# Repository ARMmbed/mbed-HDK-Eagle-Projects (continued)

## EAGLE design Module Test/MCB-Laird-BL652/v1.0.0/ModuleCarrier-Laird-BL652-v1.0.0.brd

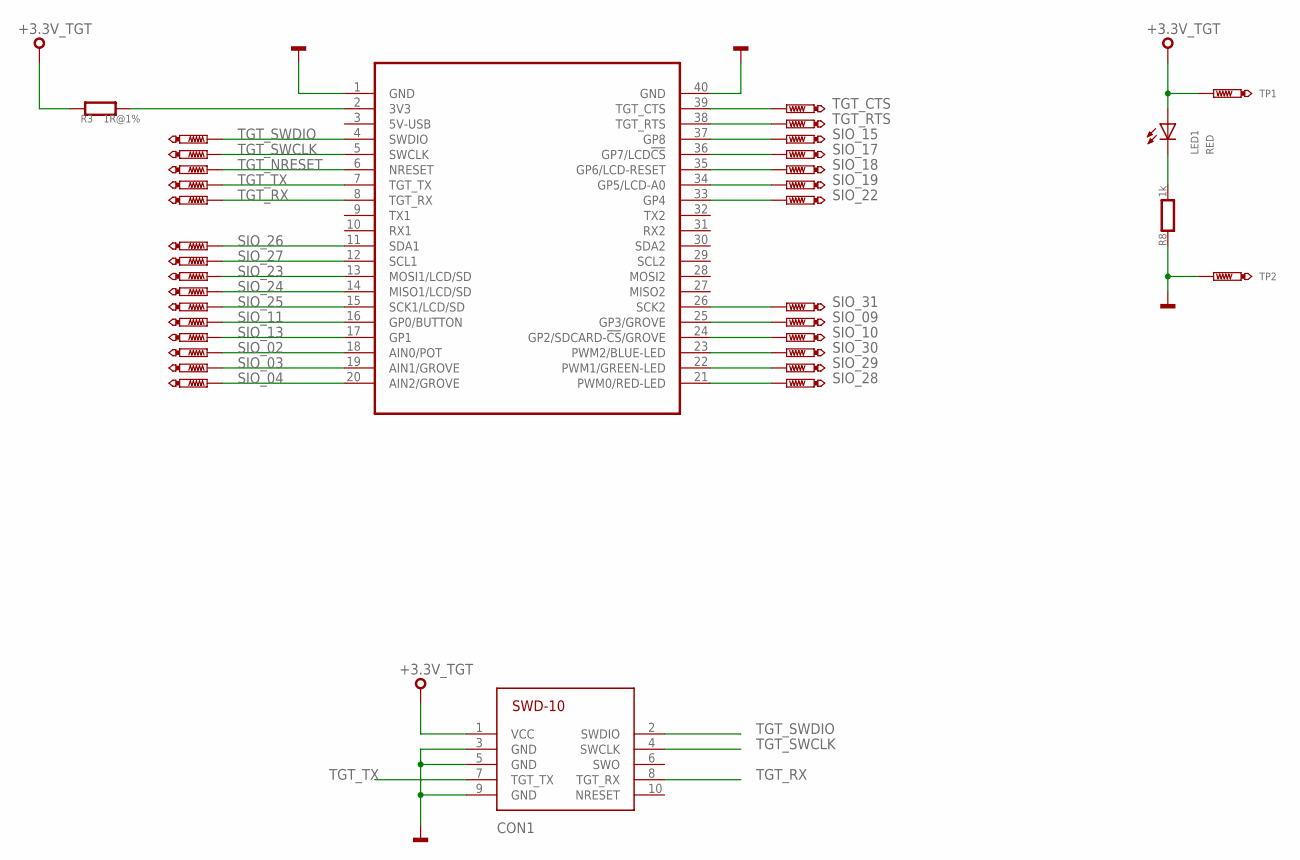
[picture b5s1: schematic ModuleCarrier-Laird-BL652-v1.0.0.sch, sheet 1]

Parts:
CON1: SWD-10/TC2050_SMD; FTSH-105-02
LED1: RED; CHIPLED_0603
MOD2: MODULE_DAUGHTER
R3: 1R@1%; 0603
R8: 1k; 0603
TP1, TP2: TEST-POINT-50R-PTH; TP50-PTH
TP3, TP4, TP5, TP6, TP7, TP8, TP9, TP10, TP11, TP12, TP13, TP14, TP15, TP16, TP17, TP18, TP19, TP20, TP21, TP22, TP23, TP24, TP25, TP26, TP27, TP28, TP29, TP30: PTR1TP07R; TP07R

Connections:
+3.3V_TGT: CON1.1 (VCC), LED1.A, R3.1, TP1.TP; also elsewhere on the board
GND: CON1.3 (GND), CON1.5 (GND), CON1.9 (GND), MOD2.1 (GND), MOD2.40 (GND), R8.1, TP2.TP; also elsewhere on the board
unnamed: MOD2.2 (3V3), R3.2
PA_1: LED1.C, R8.2
SIO_02: MOD2.18 (AIN0/POT), TP10.TP; also elsewhere on the board
SIO_03: MOD2.19 (AIN1/GROVE), TP11.TP; also elsewhere on the board
SIO_04: MOD2.20 (AIN2/GROVE), TP12.TP; also elsewhere on the board
SIO_09: MOD2.25 (GP3/GROVE), TP17.TP; also elsewhere on the board
SIO_10: MOD2.24 (GP2/SDCARD-!CS!/GROVE), TP16.TP; also elsewhere on the board
SIO_11: MOD2.16 (GP0/BUTTON), TP8.TP; also elsewhere on the board
SIO_13: MOD2.17 (GP1), TP9.TP; also elsewhere on the board
SIO_15: MOD2.37 (GP8), TP22.TP; also elsewhere on the board
SIO_17: MOD2.36 (GP7/LCD!CS), TP21.TP; also elsewhere on the board
SIO_18: MOD2.35 (GP6/LCD-RESET), TP20.TP; also elsewhere on the board
SIO_19: MOD2.34 (GP5/LCD-A0), TP19.TP; also elsewhere on the board
SIO_22: MOD2.33 (GP4), TP18.TP; also elsewhere on the board
SIO_23: MOD2.13 (MOSI1/LCD/SD), TP5.TP; also elsewhere on the board
SIO_24: MOD2.14 (MISO1/LCD/SD), TP6.TP; also elsewhere on the board
SIO_25: MOD2.15 (SCK1/LCD/SD), TP7.TP; also elsewhere on the board
SIO_26: MOD2.11 (SDA1), TP3.TP; also elsewhere on the board
SIO_27: MOD2.12 (SCL1), TP4.TP; also elsewhere on the board
SIO_28: MOD2.21 (PWM0/RED-LED), TP13.TP; also elsewhere on the board
SIO_29: MOD2.22 (PWM1/GREEN-LED), TP14.TP; also elsewhere on the board
SIO_30: MOD2.23 (PWM2/BLUE-LED), TP15.TP; also elsewhere on the board
SIO_31: MOD2.26 (SCK2), TP25.TP; also elsewhere on the board
TGT_CTS: MOD2.39 (TGT_CTS), TP24.TP; also elsewhere on the board
TGT_NRESET: MOD2.6 (NRESET), TP28.TP; also elsewhere on the board
TGT_RTS: MOD2.38 (TGT_RTS), TP23.TP; also elsewhere on the board
TGT_RX: CON1.8 (TGT_RX), MOD2.8 (TGT_RX), TP30.TP; also elsewhere on the board
TGT_SWCLK: CON1.4 (SWCLK), MOD2.5 (SWCLK), TP27.TP; also elsewhere on the board
TGT_SWDIO: CON1.2 (SWDIO), MOD2.4 (SWDIO), TP26.TP; also elsewhere on the board
TGT_TX: CON1.7 (TGT_TX), MOD2.7 (TGT_TX), TP29.TP; also elsewhere on the board

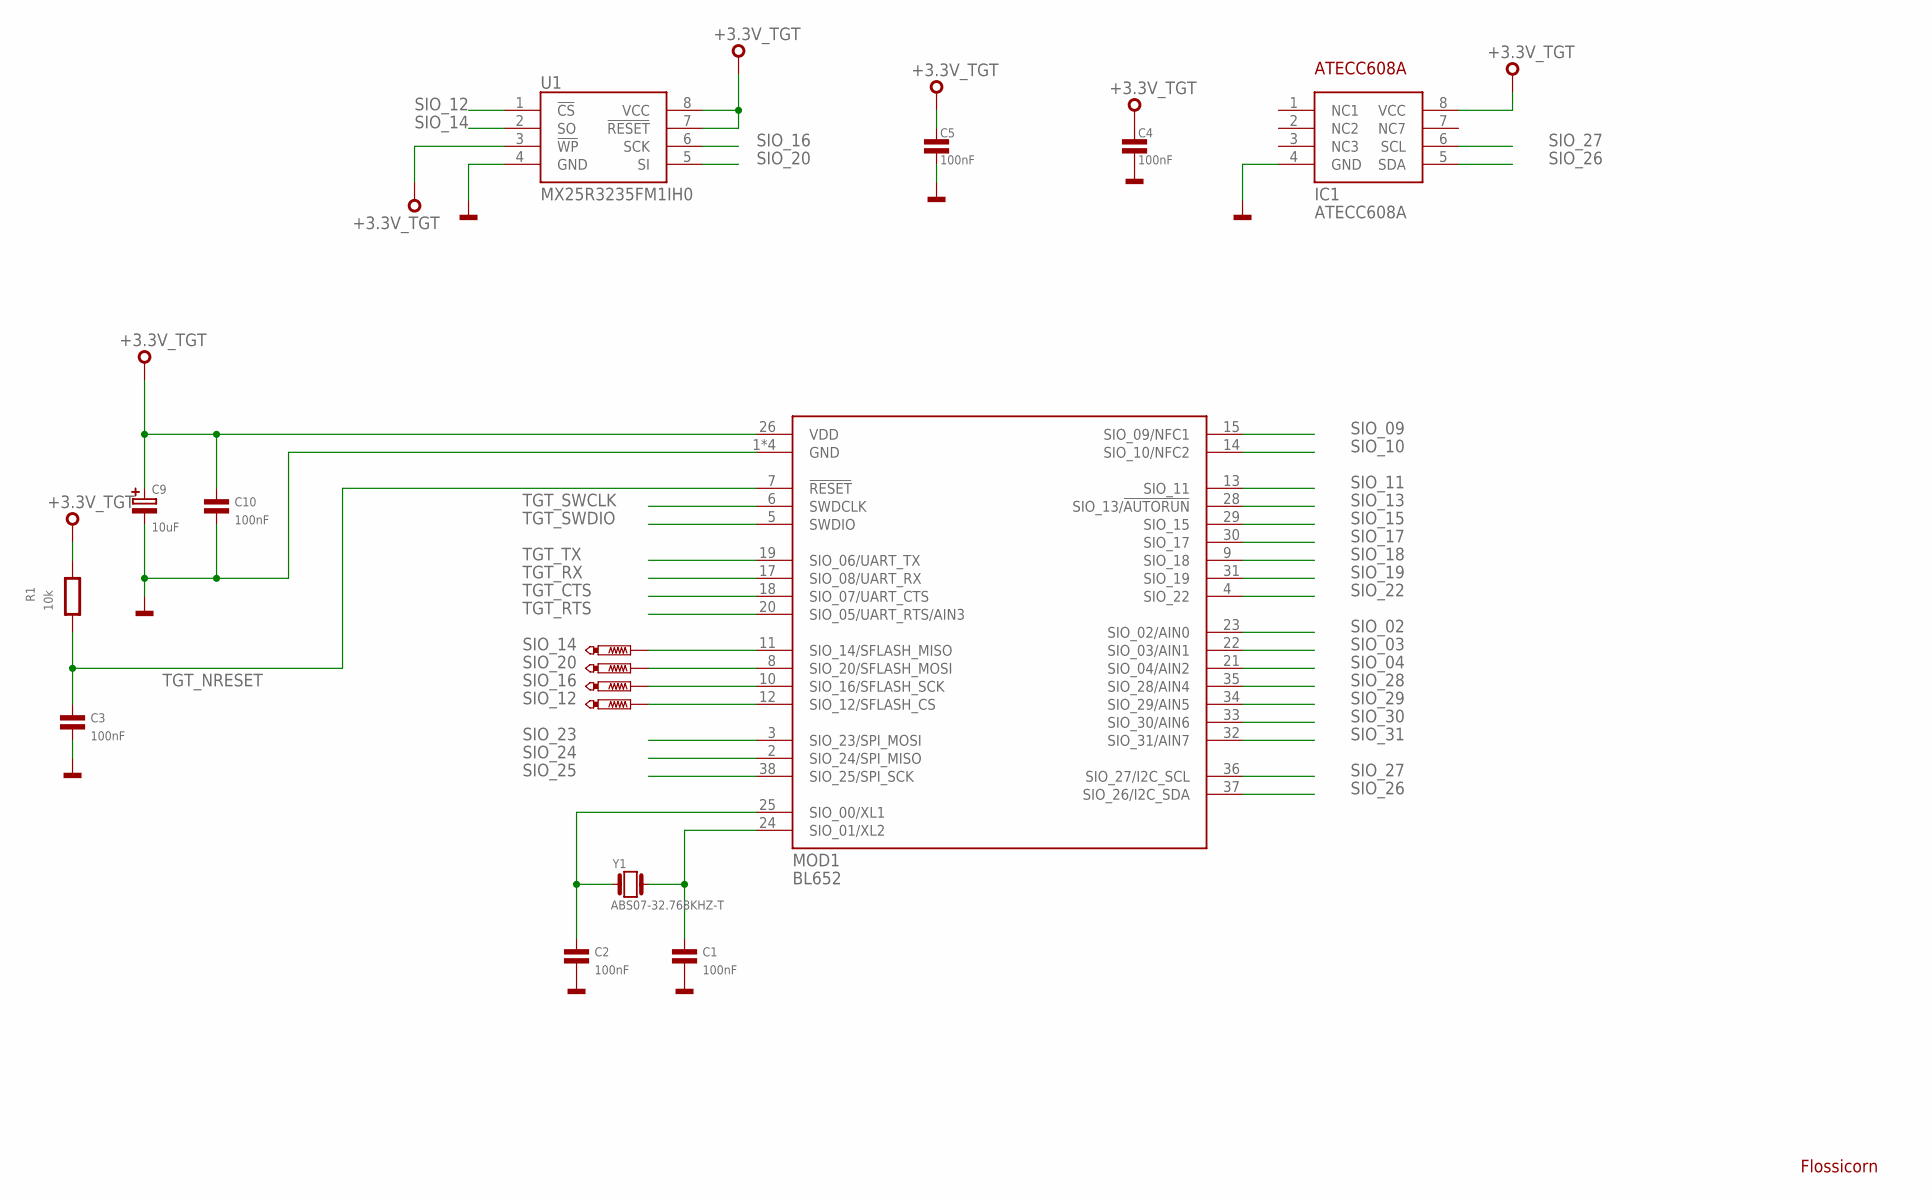
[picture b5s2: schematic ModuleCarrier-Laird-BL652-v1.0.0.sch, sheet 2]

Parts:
C1, C2, C3, C4, C5, C10: 100nF; 0603
C9: 10uF; CASE-B
IC1: ATECC608A; SO8
MOD1: BL652
R1: 10k; 0603
SS1: FLOSSICORN0.25; FLOSSICORN-0.25
TP31, TP32, TP33, TP34: PTR1TP07R; TP07R
U1: MX25R3235FM1IH0; SO8
Y1: ABS07-32.768KHZ-T; FC135

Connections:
+3.3V_TGT: C4.1, C5.1, C9.1, C10.1, IC1.8 (VCC), MOD1.26 (VDD), R1.2, U1.3 (!WP), U1.7 (!RESET), U1.8 (VCC); also elsewhere on the board
GND: C1.2, C2.2, C3.2, C4.2, C5.2, C9.2, C10.2, IC1.4 (GND), MOD1.1 (GND), MOD1.16 (GND), MOD1.27 (GND), MOD1.39 (GND), U1.4 (GND); also elsewhere on the board
unnamed: C1.1, MOD1.24 (SIO_01/XL2), Y1.X2 (2)
unnamed: C2.1, MOD1.25 (SIO_00/XL1), Y1.X1 (1)
SIO_02: MOD1.23 (SIO_02/AIN0); also elsewhere on the board
SIO_03: MOD1.22 (SIO_03/AIN1); also elsewhere on the board
SIO_04: MOD1.21 (SIO_04/AIN2); also elsewhere on the board
SIO_09: MOD1.15 (SIO_09/NFC1); also elsewhere on the board
SIO_10: MOD1.14 (SIO_10/NFC2); also elsewhere on the board
SIO_11: MOD1.13 (SIO_11); also elsewhere on the board
SIO_12: MOD1.12 (SIO_12/SFLASH_CS), TP34.TP, U1.1 (!CS)
SIO_13: MOD1.28 (SIO_13/!AUTORUN); also elsewhere on the board
SIO_14: MOD1.11 (SIO_14/SFLASH_MISO), TP31.TP, U1.2 (SO)
SIO_15: MOD1.29 (SIO_15); also elsewhere on the board
SIO_16: MOD1.10 (SIO_16/SFLASH_SCK), TP33.TP, U1.6 (SCK)
SIO_17: MOD1.30 (SIO_17); also elsewhere on the board
SIO_18: MOD1.9 (SIO_18); also elsewhere on the board
SIO_19: MOD1.31 (SIO_19); also elsewhere on the board
SIO_20: MOD1.8 (SIO_20/SFLASH_MOSI), TP32.TP, U1.5 (SI)
SIO_22: MOD1.4 (SIO_22); also elsewhere on the board
SIO_23: MOD1.3 (SIO_23/SPI_MOSI); also elsewhere on the board
SIO_24: MOD1.2 (SIO_24/SPI_MISO); also elsewhere on the board
SIO_25: MOD1.38 (SIO_25/SPI_SCK); also elsewhere on the board
SIO_26: IC1.5 (SDA), MOD1.37 (SIO_26/I2C_SDA); also elsewhere on the board
SIO_27: IC1.6 (SCL), MOD1.36 (SIO_27/I2C_SCL); also elsewhere on the board
SIO_28: MOD1.35 (SIO_28/AIN4); also elsewhere on the board
SIO_29: MOD1.34 (SIO_29/AIN5); also elsewhere on the board
SIO_30: MOD1.33 (SIO_30/AIN6); also elsewhere on the board
SIO_31: MOD1.32 (SIO_31/AIN7); also elsewhere on the board
TGT_CTS: MOD1.18 (SIO_07/UART_CTS); also elsewhere on the board
TGT_NRESET: C3.1, MOD1.7 (!RESET), R1.1; also elsewhere on the board
TGT_RTS: MOD1.20 (SIO_05/UART_RTS/AIN3); also elsewhere on the board
TGT_RX: MOD1.17 (SIO_08/UART_RX); also elsewhere on the board
TGT_SWCLK: MOD1.6 (SWDCLK); also elsewhere on the board
TGT_SWDIO: MOD1.5 (SWDIO); also elsewhere on the board
TGT_TX: MOD1.19 (SIO_06/UART_TX); also elsewhere on the board

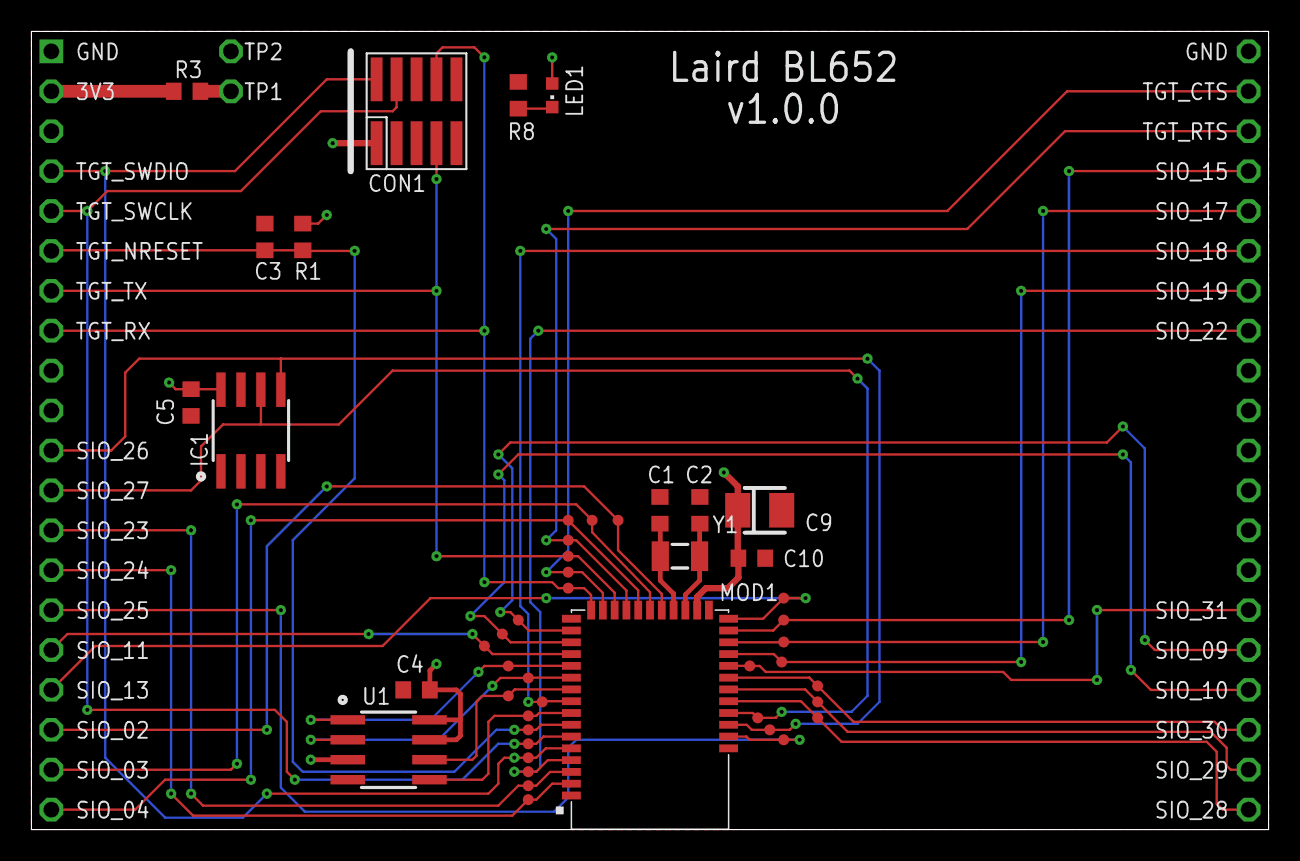
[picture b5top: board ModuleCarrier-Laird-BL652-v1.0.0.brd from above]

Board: 2 copper layers, 78.7 x 50.8 mm, 52 parts (0 on the bottom side), 38 nets.
